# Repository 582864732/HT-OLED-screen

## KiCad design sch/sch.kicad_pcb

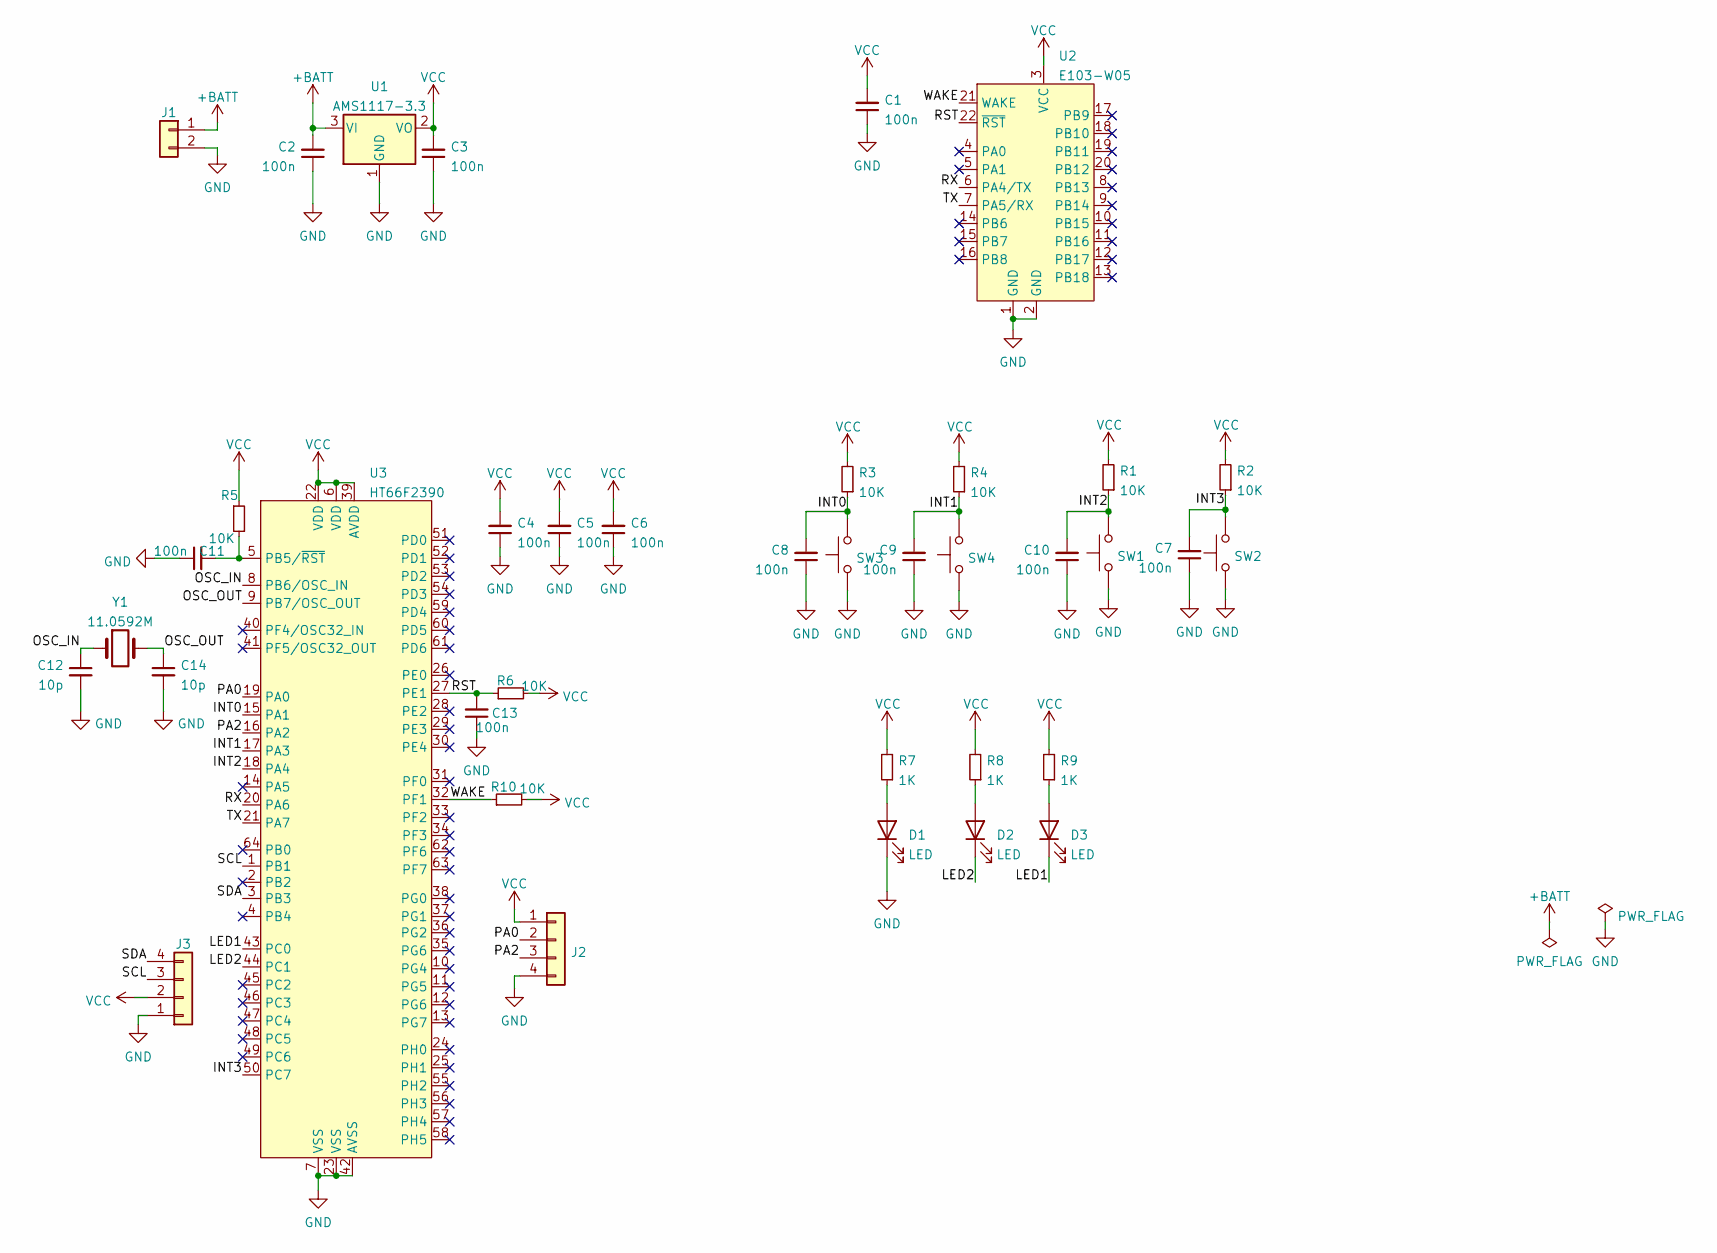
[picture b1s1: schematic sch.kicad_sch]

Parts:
C1, C2, C3, C4, C5, C6, C7, C8, C9, C10, C11, C13: 100n; C_0603_1608Metric
C12, C14: 10p; C_0603_1608Metric
D1, D2, D3: LED; LED_0603_1608Metric
J1: Conn_01x02; PinHeader_1x02_P2.54mm_Vertical
J2: Conn_01x04; PinHeader_1x04_P2.54mm_Vertical
J3: Conn_01x04; 1.3-in OLED
R1, R2, R3, R4, R5, R6, R10: 10K; R_0603_1608Metric
R7, R8, R9: 1K; R_0603_1608Metric
SW1, SW2, SW3, SW4: SW_Push; SW_Push_1P1T_NO_6x6mm_H9.5mm
U1: AMS1117-3.3; SOT-223-3_TabPin2
U2: E103-W05
U3: HT66F2390; LQFP-64_7x7mm_P0.4mm
Y1: 11.0592M; Crystal_HC49-4H_Vertical

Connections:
+BATT: C2.2, J1.1, U1.3 (VI)
/INT0: C8.2, R3.1, SW3.2, U3.15 (PA1)
/INT1: C9.2, R4.1, SW4.2, U3.17 (PA3)
/INT2: C10.2, R1.1, SW1.2, U3.18 (PA4)
/INT3: C7.2, R2.1, SW2.2, U3.50 (PC7)
/LED1: D3.1 (K), U3.43 (PC0)
/LED2: D2.1 (K), U3.44 (PC1)
/OSC_IN: C12.1, U3.8 (PB6/OSC_IN), Y1.1
/OSC_OUT: C14.1, U3.9 (PB7/OSC_OUT), Y1.2
/PA0: J2.2, U3.19 (PA0)
/PA2: J2.3, U3.16 (PA2)
/RST: C13.2, R6.1, U2.22 (~RST), U3.27 (PE1)
/RX: U2.6 (PA4/TX), U3.20 (PA6)
/SCL: J3.3, U3.1 (PB1)
/SDA: J3.4, U3.3 (PB3)
/TX: U2.7 (PA5/RX), U3.21 (PA7)
/WAKE: R10.1, U2.21 (WAKE), U3.32 (PF1)
GND: C1.1, C2.1, C3.1, C4.1, C5.1, C6.1, C7.1, C8.1, C9.1, C10.1, C11.1, C12.2, C13.1, C14.2, D1.1 (K), J1.2, J2.4, J3.1, SW1.1, SW2.1, SW3.1, SW4.1, U1.1 (GND), U2.1 (GND), U2.2 (GND), U3.7 (VSS), U3.23 (VSS), U3.42 (AVSS)
unnamed: C11.2, R5.2, U3.5 (PB5/~RST)
unnamed: D1.2 (A), R7.1
unnamed: D2.2 (A), R8.1
unnamed: D3.2 (A), R9.1
VCC: C1.2, C3.2, C4.2, C5.2, C6.2, J2.1, J3.2, R1.2, R2.2, R3.2, R4.2, R5.1, R6.2, R7.2, R8.2, R9.2, R10.2, U1.2 (VO), U2.3 (VCC), U3.6 (VDD), U3.22 (VDD), U3.39 (AVDD)

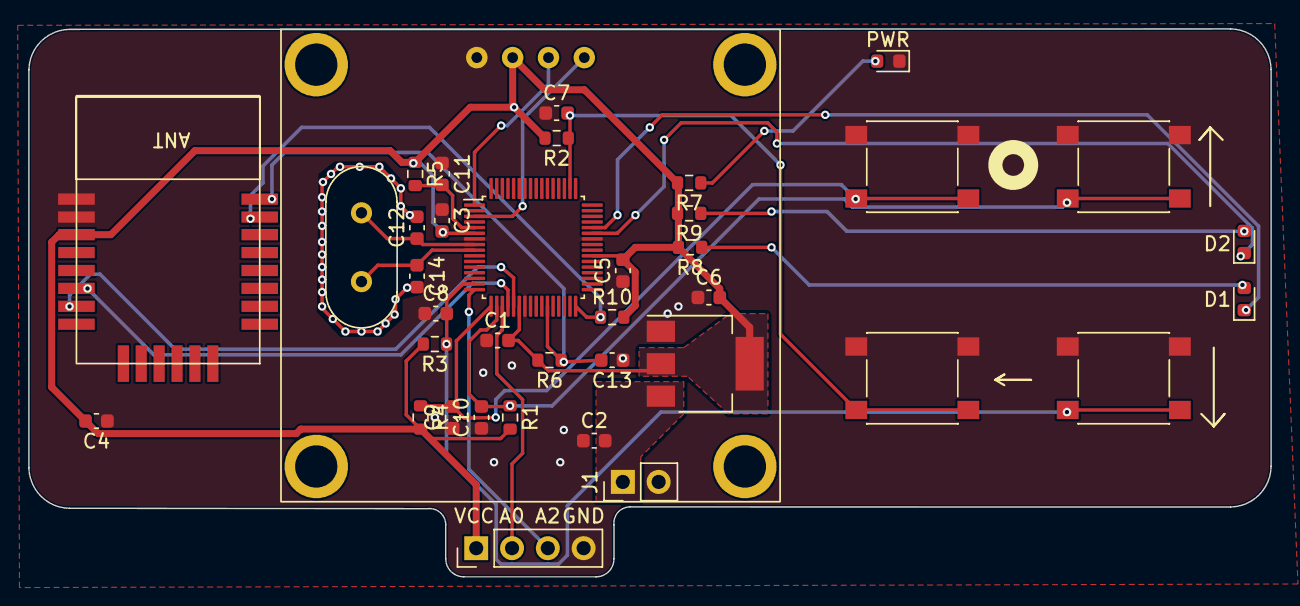
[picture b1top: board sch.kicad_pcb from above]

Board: 2 copper layers, 88.1 x 38.9 mm, 38 parts (0 on the bottom side), 23 nets.

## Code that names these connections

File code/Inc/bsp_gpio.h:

#ifndef _HT66_BSP_GPIO_H
#define _HT66_BSP_GPIO_H
#include"main.h"
#include"gpio.h"

#define int0 _pa1
#define int1 _pa3
#define int2 _pa4
#define int3 _pc7

#define led1 _pc0
#define led2 _pc1

#define led1_on() led1=0
#define led1_off() led1=1
#define led1_toggle() led1=~led1

#define led2_on() led2=0
#define led2_off() led2=1
#define led2_toggle() led2=~led2

#define GInit() GPIO_Init()

void GPIO_Init(void);

void __attribute((interrupt(0x04))) INT0_ISR(void);
void __attribute((interrupt(0x08))) INT1_ISR(void);
void __attribute((interrupt(0x30))) INT2_ISR(void);
void __attribute((interrupt(0x34))) INT3_ISR(void);

#endif

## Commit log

2022-04-01 create git
2022-04-02 add .gitignore and complete PCB
2022-04-02 add GUI logic
2022-04-02 can show bmp
2022-04-13 indentify UART baudrate add ChangeList to quick reflash OLED for GUI test AT Command
2022-04-26 complete code in base
